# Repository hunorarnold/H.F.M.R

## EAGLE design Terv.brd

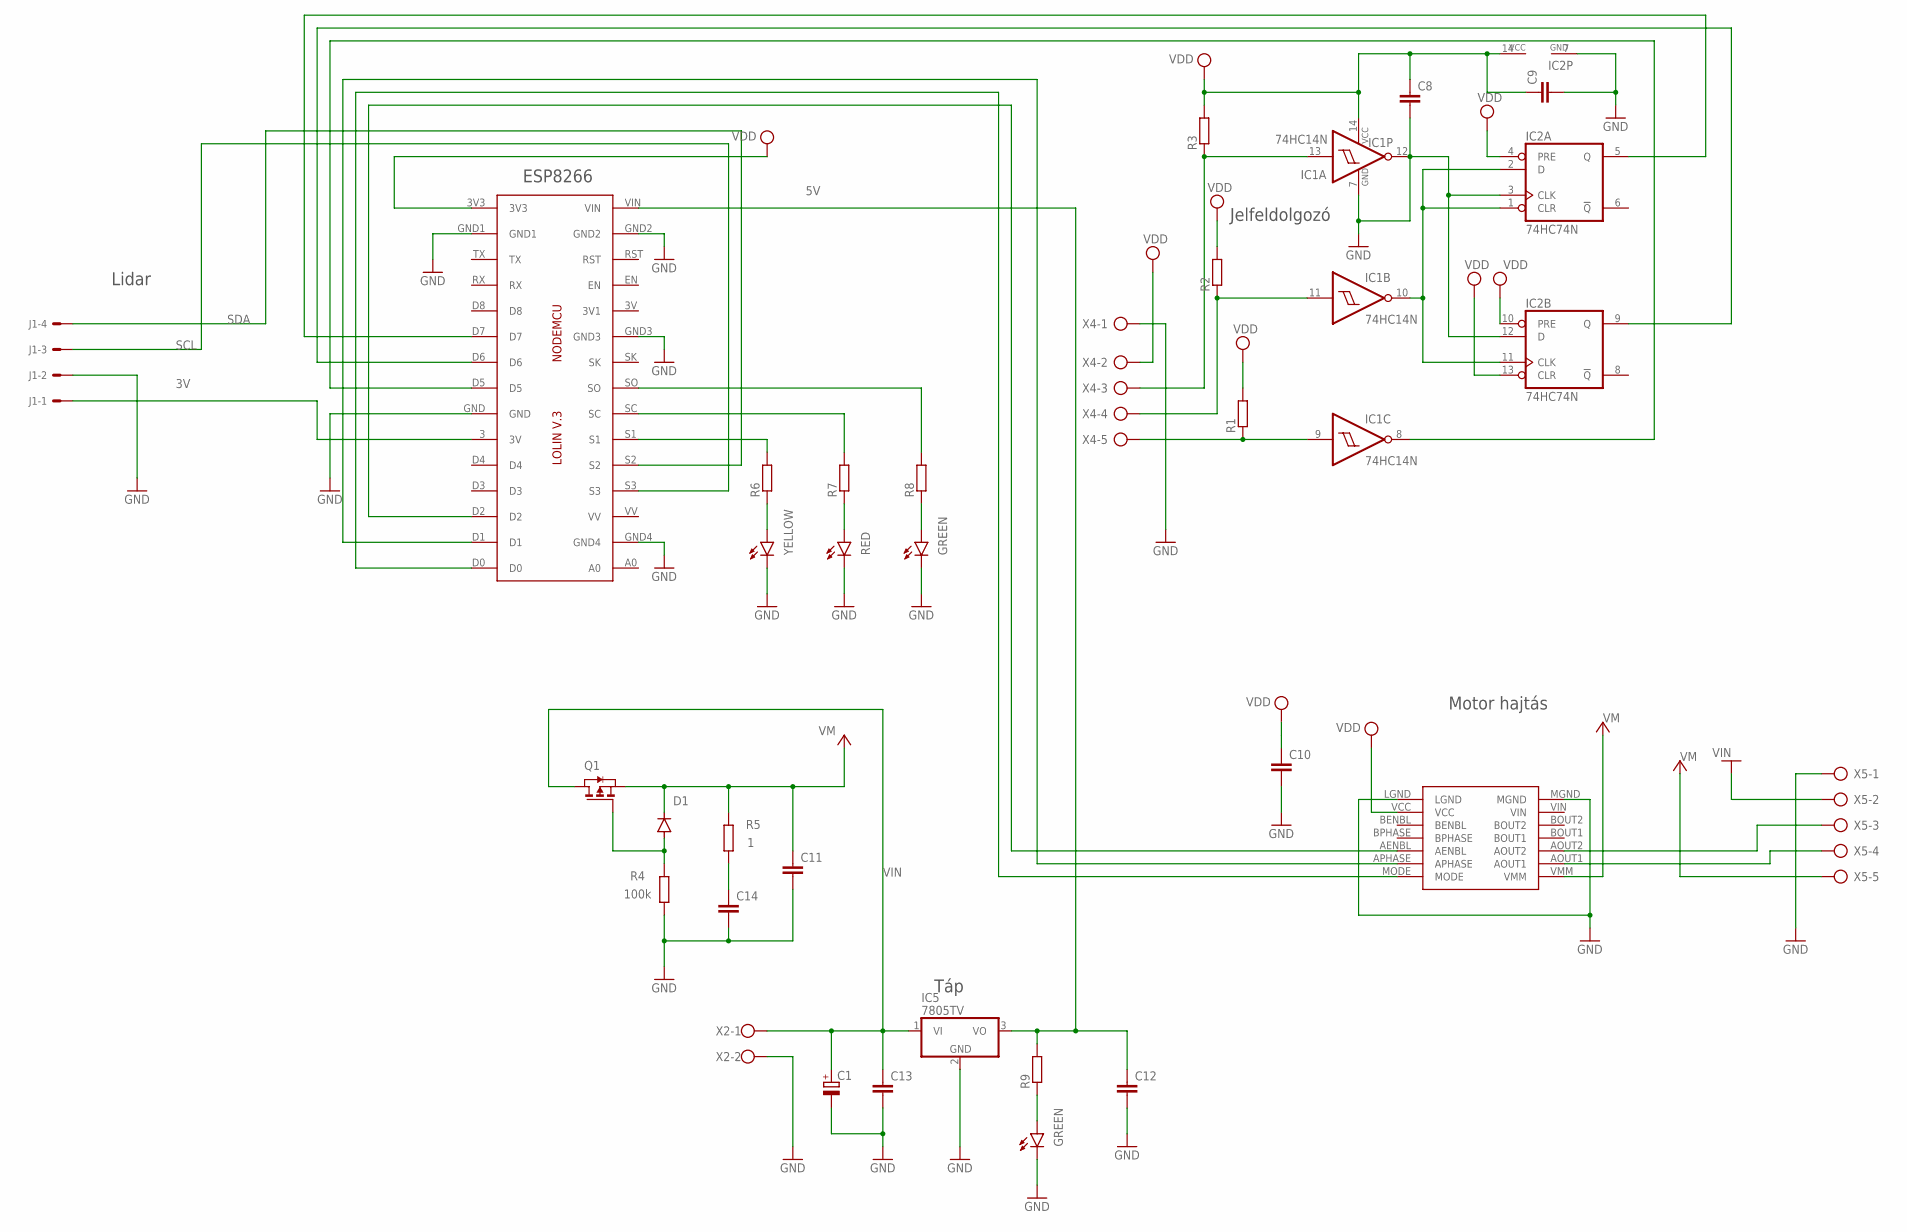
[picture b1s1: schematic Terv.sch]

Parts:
C1: CPOL-EUE2.5-6; E2,5-6
C8, C9, C10, C11, C12, C13, C14: C-EU050-025X075; C050-025X075
D1: 1N4004; DO41-10
IC1: 74HC14N; DIL14
IC2: 74HC74N; DIL14
IC4: LOLINV3
IC5: 7805TV; TO220V
J1: 22-27-2041-04; 6410-04
LED1: TLLY4400; LED3MM
LED2: TLLR4400; LED3MM
LED3, LED4: TLLG4400; LED3MM
R1, R2, R3, R4, R5, R6, R7, R8, R9: R-EU_0204/7; 0204/7
T1: PMOSE3L; E3LINE
U$1: POLOLU_MOTOR_DRV8835THROUGHHOLE; POLOLU_MOTOR_DRV_DRV8835
X2: W237-102
X4, X5: AK300/5

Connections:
3V: IC4.3 (3V), J1.1
5V: C12.1, IC4.VIN, IC5.3 (VO), R9.2
GND: C1.-, C8.2, C9.2, C10.2, C11.2, C12.2, C13.2, C14.2, IC1.7 (GND), IC1.12 (O), IC2.7 (GND), IC4.GND, IC4.GND1, IC4.GND2, IC4.GND3, IC4.GND4, IC5.2 (GND), J1.2, LED1.K (C), LED2.K (C), LED3.K (C), LED4.K (C), R4.1, U$1.LGND, U$1.MGND, X2.2, X4.1, X5.1, X5.2
unnamed: IC1.9 (I), R1.1, X4.5
unnamed: IC1.10 (O), IC2.1 (CLR), IC2.2 (D), IC2.11 (CLK)
unnamed: IC1.13 (I), R3.1, X4.3
unnamed: IC2.3 (CLK), IC2.12 (D)
unnamed: IC1.11 (I), R2.1, X4.4
unnamed: IC2.5 (Q), IC4.D7
unnamed: IC2.9 (Q), IC4.D6
unnamed: IC1.8 (O), IC4.D5
unnamed: IC4.D0, U$1.MODE
unnamed: IC4.D2, U$1.AENBL
unnamed: IC4.S1, R6.2
unnamed: U$1.AOUT2, X5.3
unnamed: U$1.AOUT1, X5.4
unnamed: D1.A, R4.2, T1.2 (G)
unnamed: C14.1, R5.1
unnamed: IC4.D1, U$1.APHASE
unnamed: IC4.SC, R7.2
unnamed: IC4.SO, R8.2
unnamed: LED1.A, R6.1
unnamed: LED2.A, R7.1
unnamed: LED3.A, R8.1
unnamed: LED4.A, R9.1
SCL: IC4.S3, J1.3
SDA: IC4.S2, J1.4
V+: C11.1, D1.C, R5.2, T1.3 (S), U$1.VMM, X5.5
VDD: C8.1, C9.1, C10.1, IC1.14 (VCC), IC2.4 (PRE), IC2.10 (PRE), IC2.14 (VCC), IC4.3V3, R1.2, R2.2, R3.2, U$1.VCC, X4.2
VIN: C1.+, C13.1, IC5.1 (VI), T1.1 (D), X2.1

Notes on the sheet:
Táp
Motor hajtás
Jelfeldolgozó
ESP8266
Lidar

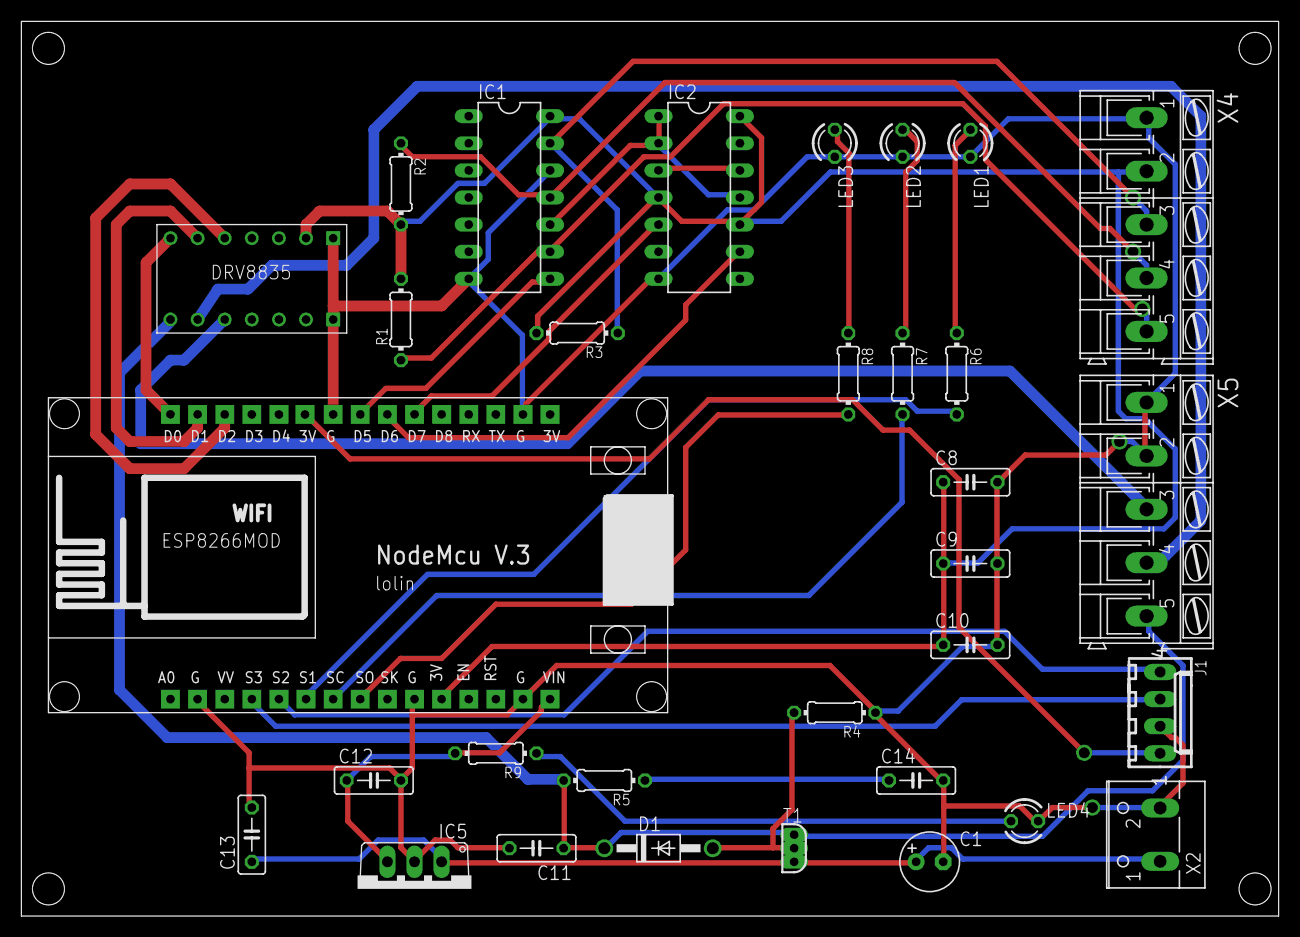
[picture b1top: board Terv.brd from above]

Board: 2 copper layers, 117.8 x 83.8 mm, 32 parts (0 on the bottom side), 30 nets.

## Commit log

2019-12-25 Plan
